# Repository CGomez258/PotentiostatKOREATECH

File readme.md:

Code for potentiostat circuit and circuit design

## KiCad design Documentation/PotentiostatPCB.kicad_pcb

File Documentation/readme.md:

This section contains the circuit design file

The circuit diagram was designed with KiCad 9.0

The ZIP file is the GERBER file for a PCB design

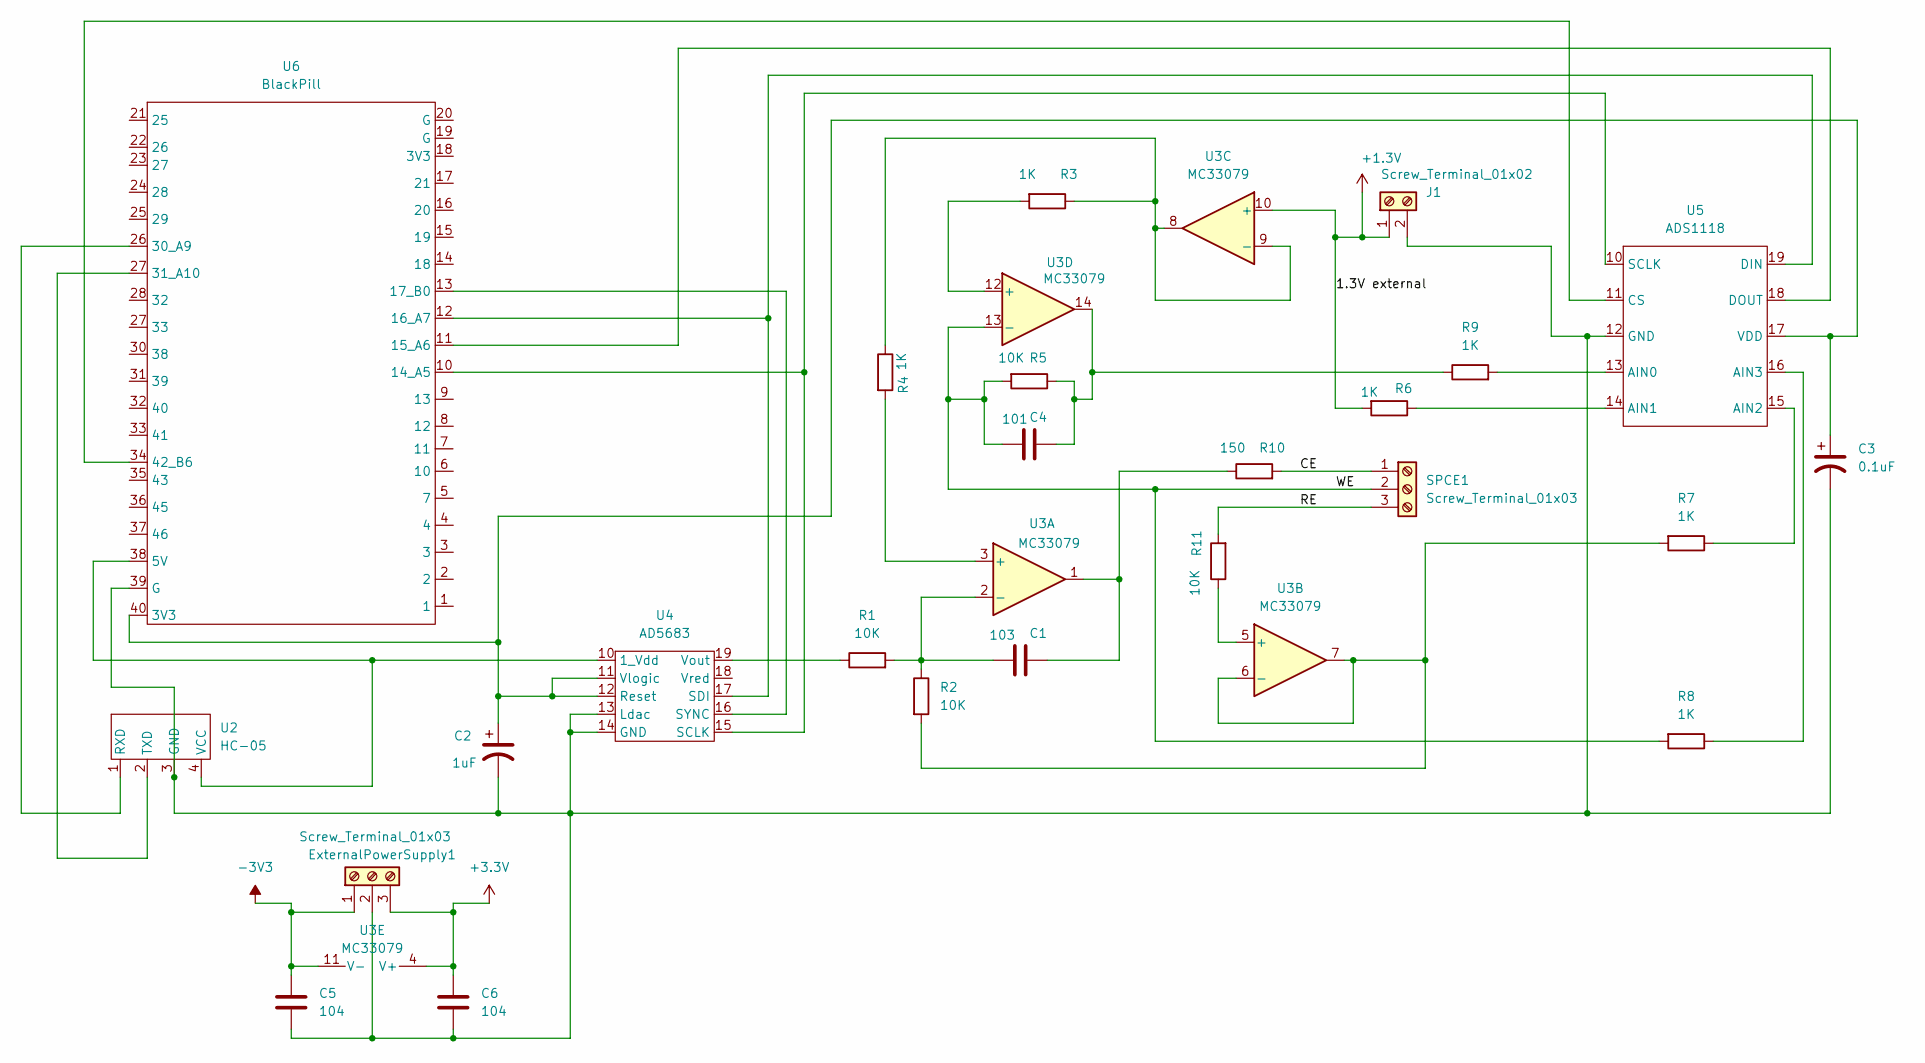
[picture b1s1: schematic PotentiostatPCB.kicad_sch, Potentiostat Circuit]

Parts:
C1: 103; CeramicCap
C2: 1uF; ElectrolitCap
C3: 0.1uF; ElectrolitCap
C4: 101; CeramicCap
C5, C6: 104; CeramicCap
ExternalPowerSupply1: Screw_Terminal_01x03; TerminalBlock_Phoenix_MKDS-1,5-3_1x03_P5.00mm_Horizontal
J1: Screw_Terminal_01x02; TerminalBlock_Phoenix_MKDS-1,5-2-5.08_1x02_P5.08mm_Horizont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
R1, R2, R5, R11: 10K; Resistor
R3, R4, R6, R7, R8, R9: 1K; Resistor
R10: 150; Resistor
SPCE1: Screw_Terminal_01x03; TerminalBlock_Phoenix_MKDS-1,5-3_1x03_P5.00mm_Horizontal
U2: HC-05; 4pinConnector
U3: MC33079; 7pinConnector
U4: AD5683; DIP-28_W15.24mm_LongPads
U5: ADS1118; DIP-28_W15.24mm_LongPads
U6: BlackPill; DIP-40_W15.24mm_LongPads

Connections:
+1.3V: J1.1, R6.2, U3.10 (+)
+3.3V: C6.1, ExternalPowerSupply1.3, U3.4 (V+)
-3V3: C5.1, ExternalPowerSupply1.1, U3.11 (V-)
/CE: R10.2, SPCE1.1
/RE: R11.2, SPCE1.3
/WE: C4.1, R5.2, R8.2, SPCE1.2, U3.13 (-)
unnamed: C1.2, R10.1, U3.1
unnamed: C4.2, R5.1, R9.1, U3.14
unnamed: C2.2, C3.2, C5.2, C6.2, ExternalPowerSupply1.2, J1.2, U2.3 (GND), U4.13 (Ldac), U4.14 (GND), U5.12 (GND), U6.39 (G)
unnamed: U2.1 (RXD), U6.26 (30_A9)
unnamed: U2.2 (TXD), U6.27 (31_A10)
unnamed: U2.4 (VCC), U4.10 (1_Vdd), U6.38 (5V)
unnamed: R4.2, U3.3 (+)
unnamed: C1.1, R1.2, R2.1, U3.2 (-)
unnamed: R11.1, U3.5 (+)
unnamed: R2.2, R7.2, U3.6 (-), U3.7
unnamed: R3.1, R4.1, U3.8, U3.9 (-)
unnamed: R3.2, U3.12 (+)
unnamed: C2.1, C3.1, U4.11 (Vlogic), U4.12 (Reset), U5.17 (VDD), U6.40 (3V3)
unnamed: U4.15 (SCLK), U5.10 (SCLK), U6.10 (14_A5)
unnamed: U4.17 (SDI), U5.19 (DIN), U6.12 (16_A7)
unnamed: U4.16 (SYNC), U6.13 (17_B0)
unnamed: R1.1, U4.19 (Vout)
unnamed: R9.2, U5.13 (AIN0)
unnamed: R6.1, U5.14 (AIN1)
unnamed: R7.1, U5.15 (AIN2)
unnamed: R8.1, U5.16 (AIN3)
unnamed: U5.11 (CS), U6.34 (42_B6)
unnamed: U5.18 (DOUT), U6.11 (15_A6)

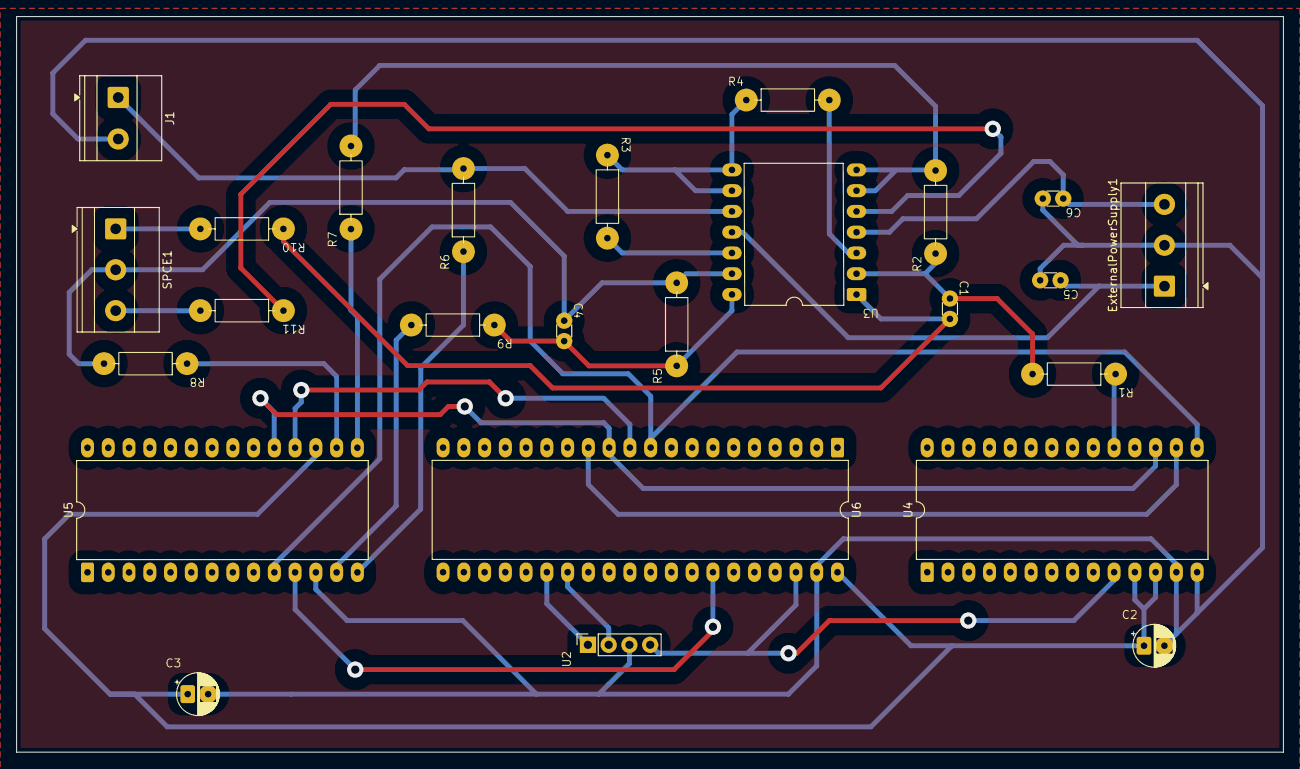
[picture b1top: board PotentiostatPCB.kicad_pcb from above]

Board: 2 copper layers, 155.0 x 90.0 mm, 25 parts (0 on the bottom side), 29 nets.

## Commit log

2026-03-20 Add description for potentiostat circuit project
2026-03-20 Add readme.md for potentiostat circuit setup
2026-03-20 Add circuit design file section to README
2026-03-20 Update readme with Arduino configuration image
    Added an image to the readme for Arduino configuration.
2026-03-20 Update readme with image for Arduino configuration
    Added an image to enhance the readme instructions.
2026-03-22 Update readme with circuit design details
